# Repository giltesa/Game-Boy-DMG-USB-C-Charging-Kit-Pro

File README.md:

# Game Boy DMG: USB-C Charging Kit PRO

The **Game Boy DMG USB-C Charging Kit PRO** is a new circuit designed specifically for the **Nintendo Game Boy**. This all-in-one circuit includes not only the **charging controller** but also a **boost converter** and **audio amplifier**.

The modern **IPS displays** with backlighting require more power than the original display, and **flash cards** used to load tons of games can quickly drain the battery. To truly enjoy the games, it is recommended to use a rechargeable battery instead of AA batteries.

However, simply using a rechargeable battery is not sufficient. The increased power consumption puts a strain on the original electronics, potentially causing noise in the speaker or headphones.

The typical solution is to add a charging circuit for the battery and a power converter to replace the old, inefficient one included in the GB. Some individuals also add an audio amplifier to enhance the sound quality of the speaker. All these modifications make the GBP function optimally. However, installing them requires numerous cables and may be challenging for individuals without sufficient knowledge.

This board adds all these features with a clean and straightforward installation:

## Would you like it?

https://shop.giltesa.com/product/game-boy-dmg-usb-c-charging-kit/

## More

- [giltesa.com](https://giltesa.com "giltesa.com")
- [twitter.com](https://twitter.com/giltesa "twitter.com")

## License

This project is licensed under a **Creative Commons** license:
**[Attribution-NonCommercial-ShareAlike 4.0 International (CC BY-NC-SA 4.0) ](https://creativecommons.org/licenses/by-nc-sa/4.0/)**

Check the [LICENSE.md](LICENSE.md) for more information.

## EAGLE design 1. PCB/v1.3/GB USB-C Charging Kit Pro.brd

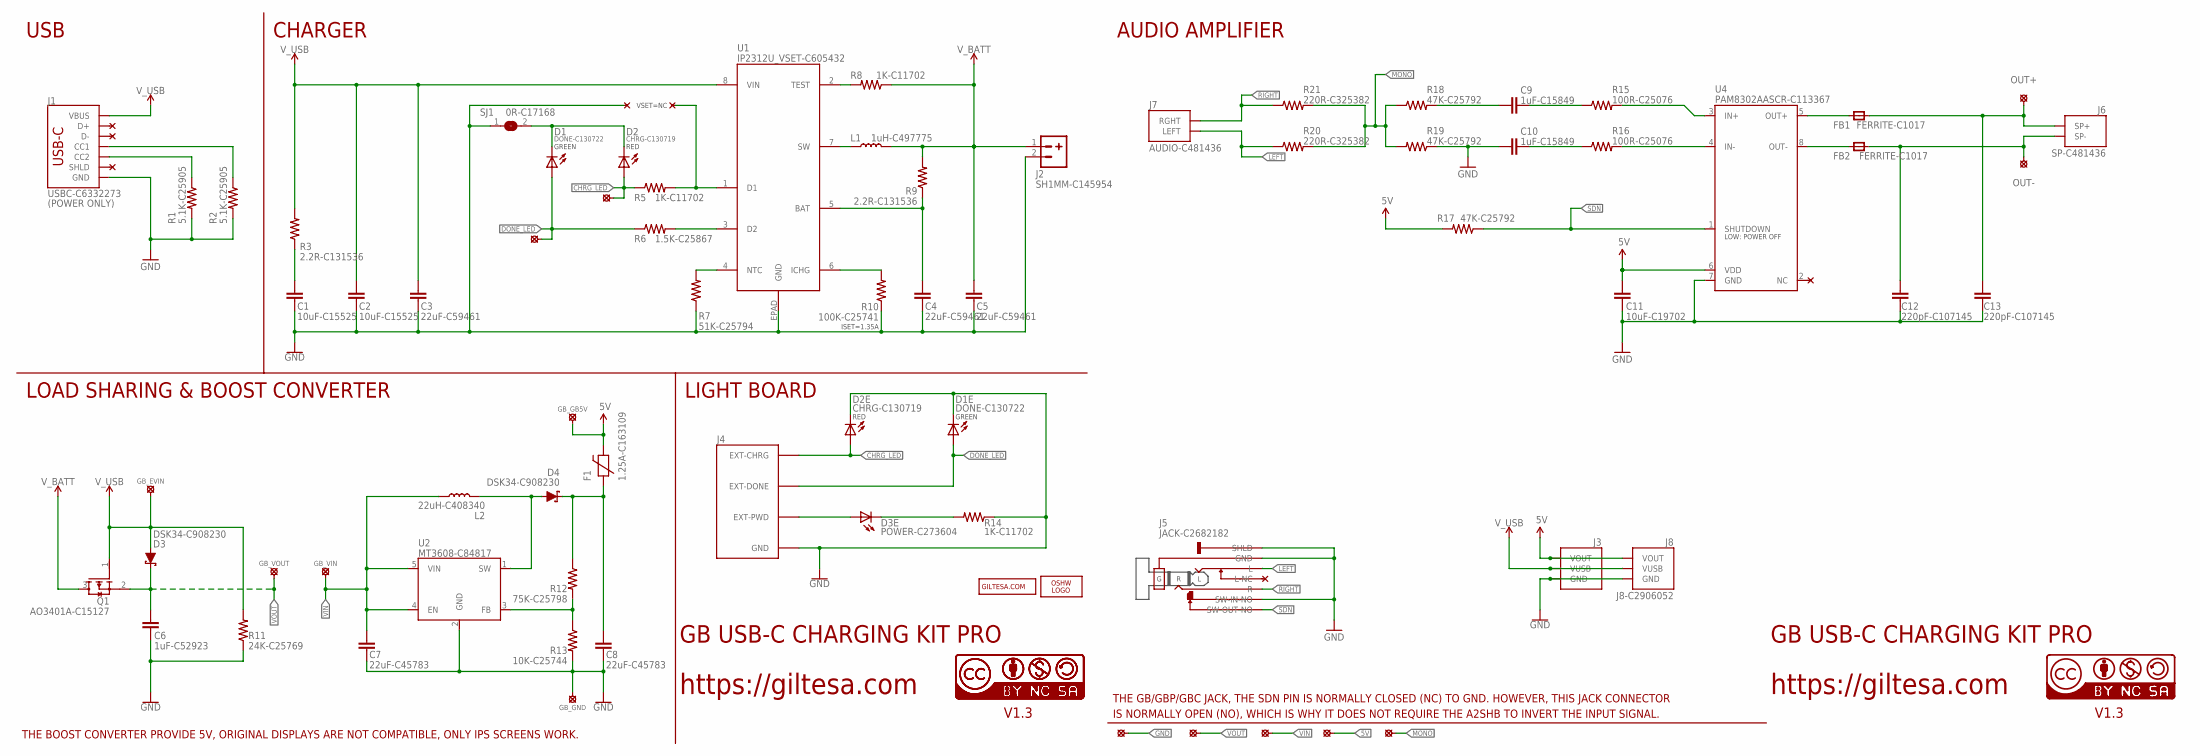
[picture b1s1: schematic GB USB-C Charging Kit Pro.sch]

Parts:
C1, C2: 10uF-C15525; C0402_S
C3, C4, C5: 22uF-C59461; C0603_S
C6: 1uF-C52923; C0402_S
C7, C8: 22uF-C45783; C0805_S
C9, C10: 1uF-C15849; C0603_S
C11: 10uF-C19702; C0603_S
C12, C13: 220pF-C107145; C0805_S
D1, D1E: DONE-C130722; L0402
D2, D2E: CHRG-C130719; L0402
D3, D4: DSK34-C908230; SOD-123FL
D3E: POWER-C273604; L0402
F1: 1.25A-C163109; F0603_S
FB1, FB2: FERRITE-C1017; MICROBUILDER__0805MP_S
GBL_: LED-C481436; GB_DMG_JST_LED
GB_: POWER-C2845538; GB_DMG_JST_POWER
J1: USBC-C6332273; USB-C_16P_3MM
J2: SH1MM-C145954; JST-2-1MM-SMD_RIGHT
J3: GB_DMG_BRIDGE_2.0MM_UP
J4: GB_DMG_LED
J5: JACK-C2682182; GB_DMG_JACK
J6: SP-C481436; GB_DMG_JST_SPEAKER
J7: AUDIO-C481436; GB_DMG_JST_AUDIO
J8: J8-C2906052; GB_DMG_BRIDGE_2.0MM_RIGHT
L1: 1uH-C497775; PSPMAA0402
L2: 22uH-C408340; PSPMAA0402
LOGO2: OSHW_LOGO_FILLX0150-NT; OSHW_FILLX150_NOTEXT
PP1, PP2, PP3, PP4, PP6: SOLDER_PAD-1.3; SOLDER_PAD_1.3
Q1: AO3401A-C15127; SOT23-3_S
R1, R2: 5.1K-C25905; R0402
R3, R9: 2.2R-C131536; R0402
R5, R8, R14: 1K-C11702; R0402
R6: 1.5K-C25867; R0402
R7: 51K-C25794; R0402
R10: 100K-C25741; R0402
R11: 24K-C25769; R0402
R12: 75K-C25798; R0402
R13: 10K-C25744; R0402
R15, R16: 100R-C25076; R0402
R17, R18, R19: 47K-C25792; R0402
R20, R21: 220R-C325382; R0402
SJ1: 0R-C17168; JUMPER-SMD_0402
U1: IP2312U_VSET-C605432; IP2312
U2: MT3608-C84817; SOT-23-6
U4: PAM8302AASCR-C113367; PAM8302AASCR
U$6: CC-BY-NC-SA15MM; CC-BY-NC-SA_15MM
U$16: GILTESA.COM_MASK; GILTESA.COM_MASK_15MM
U$17, U$21: CC-NC-BCNIX; CC-NC-B_NIX
U$20: OUT+; SOLDER_PAD_1.3
U$23: OUT-; SOLDER_PAD_1.3

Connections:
5V: C11.1, F1.2, GB_.GB5V, J3.VOUT, J8.VOUT, PP1.P$1, R17.2, U4.6 (VDD)
CHRG_LED: D2.A, D2E.A, GBL_.CHRG, J4.EXT-CHRG, R5.1
DONE_LED: D1.A, D1E.A, GBL_.DONE, J4.EXT-DONE, R6.1
GND: C1.1, C2.1, C3.1, C4.1, C5.1, C6.2, C7.1, C8.1, C10.2, C11.2, C12.2, C13.2, D1E.C, D2E.C, GB_.GND, J1.GND1 (GND), J1.GND2 (GND), J2.2, J3.GND, J4.PWD-GND (GND), J4.PWD-GND' (GND), J5.1 (GND), J5.1" (GND), J5.5 (SW-IN-NO), J5.8 (SHLD), J5.8' (SHLD), J8.GND, PP2.P$1, R1.2, R2.2, R7.1, R10.1, R11.1, R13.2, R14.1, R19.1, SJ1.1, U1.EPAD (GND), U2.2 (GND), U4.7 (GND)
LEFT: J5.3 (L), J7.LEFT, R20.1
MONO: PP6.P$1, R18.1, R19.2, R20.2, R21.2
unnamed: D1.C, D2.C, SJ1.2
unnamed: C8.2, D4.C, F1.1, R12.1
unnamed: D4.A, L2.P$2 (2), U2.1 (SW)
unnamed: J1.B5-CC2 (CC2), R1.1
unnamed: R8.2, U1.2 (TEST)
unnamed: R12.2, R13.1, U2.3 (FB)
unnamed: R16.2, U4.4 (IN-)
unnamed: D3E.A, J4.EXT-PWD
unnamed: D3E.C, R14.2
unnamed: R15.2, U4.3 (IN+)
unnamed: J1.A5-CC1 (CC1), R2.1
unnamed: C4.2, R9.1, U1.5 (BAT)
unnamed: C1.2, R3.1
unnamed: C10.1, R16.1
unnamed: FB2.1, U4.8 (OUT-)
unnamed: R5.2, U1.1 (D1)
unnamed: FB1.1, U4.5 (OUT+)
unnamed: C9.1, R15.1
unnamed: C9.2, R18.2
unnamed: R7.2, U1.4 (NTC)
unnamed: R10.2, U1.6 (ICHG)
unnamed: R6.2, U1.3 (D2)
unnamed: L1.P$1 (1), U1.7 (SW)
OUT+: C13.1, FB1.2, J6.SP+, U$20.P$1
OUT-: C12.1, FB2.2, J6.SP-, U$23.P$1
RIGHT: J5.2 (R), J7.RGHT, R21.1
SDN: J5.6 (SW-OUT-NO), R17.1, U4.1 (SHUTDOWN)
VIN: C7.2, GB_.VIN, L2.P$1 (1), PP3.P$1, U2.4 (EN), U2.5 (VIN)
VOUT: C6.1, D3.C, GB_.VOUT, PP4.P$1, Q1.2 (S)
V_BATT: C5.2, J2.1, L1.P$2 (2), Q1.3 (D), R8.1, R9.2
V_USB: C2.2, C3.2, D3.A, GB_.EVIN, J1.VBUS1 (VBUS), J1.VBUS2 (VBUS), J3.VUSB, J8.VUSB, Q1.1 (G), R3.2, R11.2, U1.8 (VIN)

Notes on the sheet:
GB USB-C CHARGING KIT PRO
https://giltesa.com
V1.3
(POWER ONLY)
THE BOOST CONVERTER PROVIDE 5V, ORIGINAL DISPLAYS ARE NOT COMPATIBLE, ONLY IPS SCREENS WORK.
USB
CHARGER
LOAD SHARING & BOOST CONVERTER
AUDIO AMPLIFIER
LIGHT BOARD
ISET=1.35A
GREEN
RED
VSET=NC
THE GB/GBP/GBC JACK, THE SDN PIN IS NORMALLY CLOSED (NC) TO GND. HOWEVER, THIS JACK CONNECTOR
IS NORMALLY OPEN (NO), WHICH IS WHY IT DOES NOT REQUIRE THE A2SHB TO INVERT THE INPUT SIGNAL.

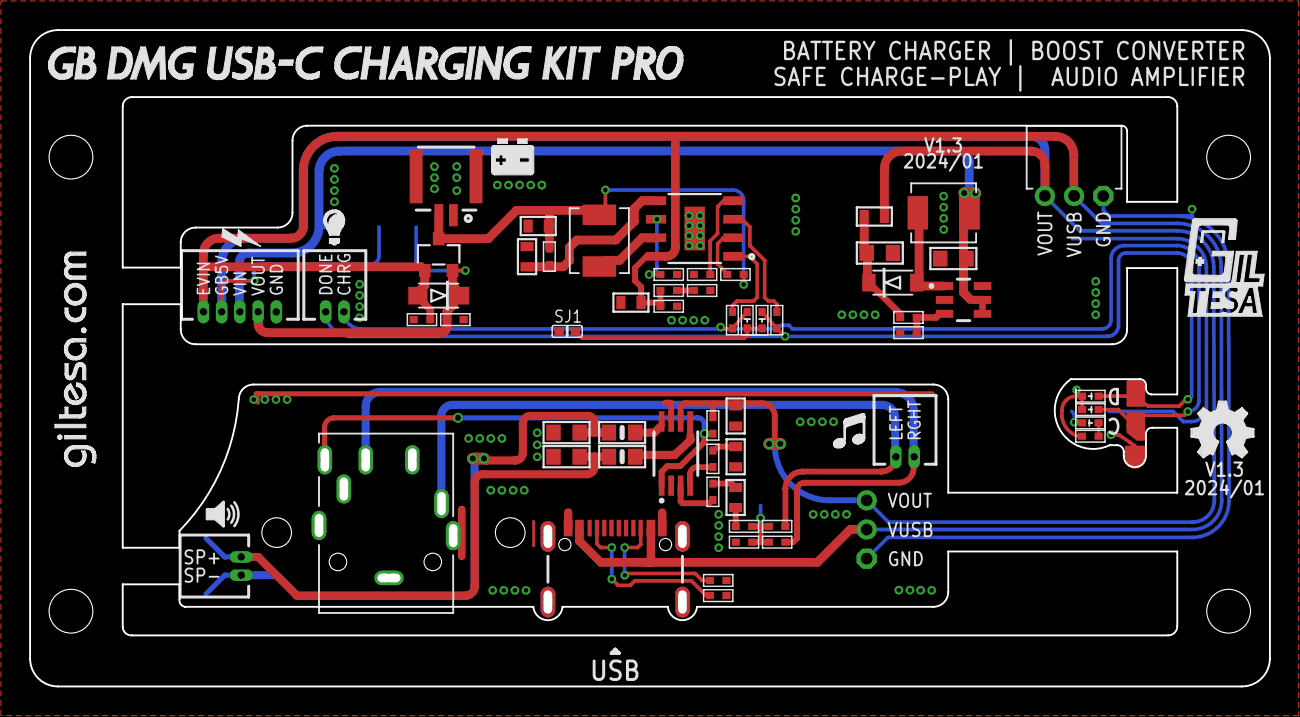
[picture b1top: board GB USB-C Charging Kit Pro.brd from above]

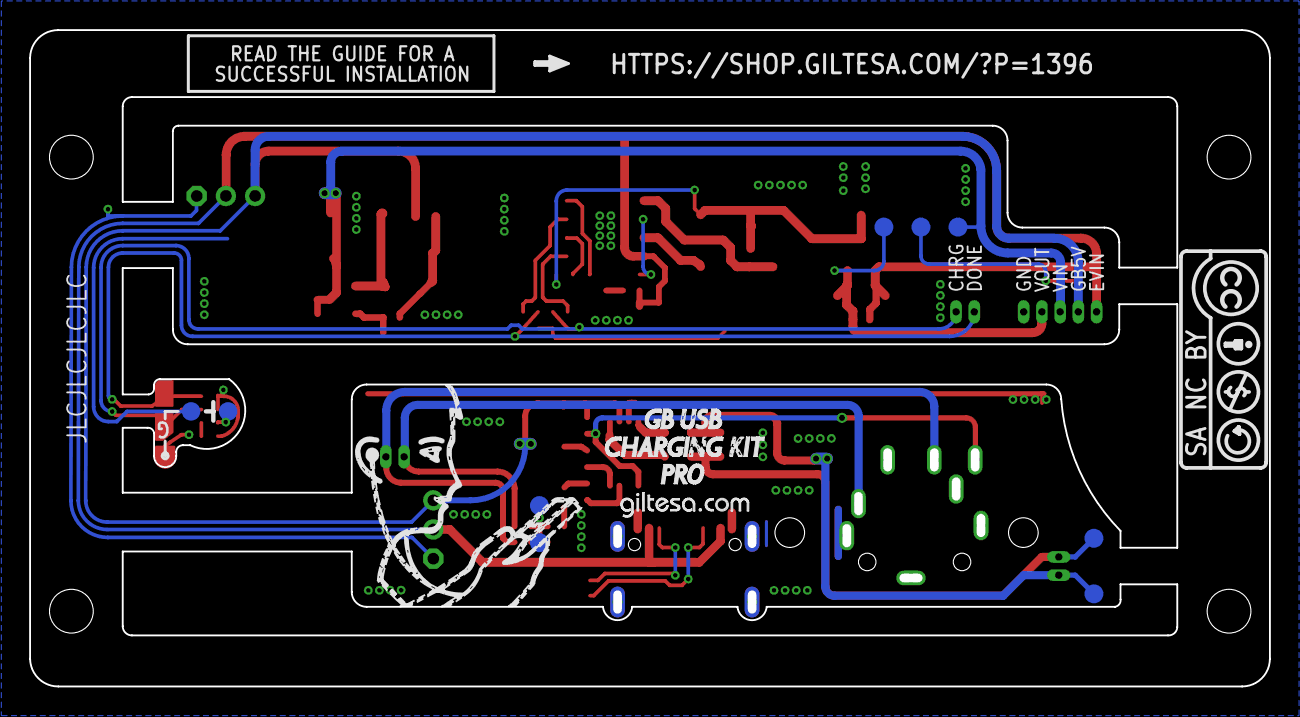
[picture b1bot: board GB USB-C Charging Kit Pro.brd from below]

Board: 2 copper layers, 85.0 x 45.0 mm, 82 parts (11 on the bottom side), 37 nets.

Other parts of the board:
U$1: SPEAKER
U$4: BATTERY
U$7: GAME_BOY_DMG
U$8: LIGHT
U$9: GILTESA_LOGO_MASK_7MM
U$10: SOUND
U$13: GB_DMG_BOARD_LOGO
U$14: POWER
U$15: GILTESA.COM_MASK_9MM
U$34: GB_DMG_BOARD

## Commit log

2023-08-14 no message
2025-01-11 v1.0
2025-01-11 v1.1
2025-01-11 v1.2
2025-01-11 v1.3

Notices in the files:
parts and their libraries:
SparkFun: Licensing: CC v3.0 Share-Alike You are welcome to use this library for commercial purposes.
SparkFun-PowerSymbols: Licensing: Creative Commons ShareAlike 4.0 International - https://creativecommons.org/licenses/by-sa/4.0
cc-by-nc-sa: All hardware is licensed under the Creative Commons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
